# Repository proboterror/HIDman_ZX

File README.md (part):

# HIDman ZX
Адаптер USB и PS/2 клавиатур/мышей для ZX Spectrum.

## Входные требования:
- Разработать универсальный простой в повторении недорогой открытый интерфейс USB / PS/2 клавиатур и мышей.
- Должны поддерживаться как минимум два USB устройства одновременно
- Включает прошивку микроконтроллера, референсную минимальную схему включения и пример тестовой платы в KiCad
- Основной фокус на сопровождаемости прошивки микроконтроллера
- Выход интерфейса клавиатуры: сигналы матрицы переключателей A8-A15, D0-D4
- Выход интерфейсов Kempston Mouse и Kempston Joystick: сигналы DI0-DI7, стробы записи регистров MX, MY, MKEY, JOY

**Дополнительно:**
- Поддержка USB HID геймпадов как Kempston Joystick и для эмуляции кнопок клавиатуры
- Выход сигналов для управления кнопками эмулятора дисковода GOTEK по горячим кнопкам клавиатуры
- Выход сигналов управления Z80 по горячим кнопкам клавиатуры: BUSRQ (PAUSE), NMI(MAGIC), RESET

**Не входит в требования:**
- Реализация платы для ZX-BUS
- Реализация портов и регистров контроллеров ZX клавиатуры и Kempston Mouse
- Реализация защиты портов USB от статики / короткого замыкания / повышенного напряжения

## Реализация
В качестве основы проекта был взят проект [HIDman](https://github.com/rasteri/HIDman): USB HID to XT / AT / PS/2 / Serial converter : адаптер USB устройств в PS/2 keyboard/mouse device. От HIDman была взята реализация стека USB Host без модификаций.

Схема использует недорогие доступные чипы от [Nanjing Qinheng Microelectronics](https://www.wch-ic.com):
- 8-bit Enhanced USB MCU [CH559L](./doc/8-bit%20Enhanced%20USB%20MCU%20CH559%20Datasheet%201.6.pdf): расширенный Intel 8051 совместимый микроконтроллер с двумя аппаратными USB Host
- 8x16 Analog Switch Array Chip [CH446Q](./doc/8x16%20Analog%20Switch%20Array%20Chip%20CH446Q%20Datasheet%201D.pdf): матрица аналоговых ключей 8x16 с последовательным интерфейсом

В код добавлены:
- Реализация асинхронных интерфейсов PS/2 клавиатуры и мыши
- Реализация матрицы контактов 8x5 ZX Spectrum клавиатуры с раскладкой Xrust
- Интерфейс матрицы ключей CH446Q
- Интерфейс для контроллера Kempston Mouse (DI+MX/MY/MKEY)
- Интерфейс для контроллера Kempston Joystick (DI+JOY)
- Интерфейс управления Z80 (PAUSE/MAGIC/RESET) по клавишам F10/F11/F12
- Интерфейс управления кнопками GOTEK (RIGHT/LEFT/SELCT) по сочетанию клавиш CTRL+ RIGHT/LEFT/DOWN/UP

## Детали реализации

Тестовая плата для отладки присоединяется сверху к [ZX Spectrum Pentagon 128 2023/2024 Interface Board](https://github.com/proboterror/Pentagon_128_Interface_Board). Исходя из этого выбраны физические размеры и положение / распиновка разъема клавиатуры.

Интерфейс мыши расчитан на подсоединение к контроллеру, подобному [ZX_BUS_Mouse](https://github.com/proboterror/ZX_BUS_Mouse) с параллельной записью по шине 8-bit в регистры осей и колеса/кнопок. Колесо прокрутки мыши поддержано.

Исходный код поддержки PS/2 клавиатуры и интерфейса матрицы ZX Spectrum => CH446Q портирован из проекта расширенного интерфейса [ZX_RGBI2VGA-HDMI + GOTEK FlashFloppy I2C OSD + PS/2 Keyboard](https://github.com/proboterror/zx-rgbi-to-vga-hdmi_gotek-osd)

Исходный код поддержки PS/2 мыши портирован из экспериментальной ветки interrupt_processing_async проекта [ZX BUS Mouse](https://github.com/proboterror/ZX_BUS_Mouse/tree/interrupt_processing_async). Код обработки мыши по прерыванию clock в свою очередь основан на проекте Олега Трифонова [avr-mouse-ps2-to-serial](https://github.com/trol73/avr-mouse-ps2-to-serial). Код инициализации PS/2 мыши и основной цикл обработки событий асинхронный с минимальными задержками.

Тестирование показало, что MCU CH559L может работать от внутреннего генератора без использования внешнего кварцевого резонатора, выбор источника частоты из кода инициализации PLL.<br>
Конденсатор и резистор цепочки сброса MCU CH559L не нужны, т.к. есть внутренняя схема формирования сброса по питанию.

При тестировании проявился дефект: после подачи питания Gluk Reset Service всегда выводит экран Help, после нажатия Reset Z80 стартует нормально. Зажата клавиша 'A' ZX клавиатуры (адрес переключателя в матрице CH449Q 0x01) до момента программного зануления всех переключателей в CH449Q.<br>
В варианте с MCU RP2040 дефект не проявлялся.<br>
Расследование показало, что RP2040 при включении переводит (большинство) GPIO в режим input c pull-down (подтяжка к земле), выдавая логический '0' на GPIO pin. MCU CH559 при подаче питания активирует для портов pull-up резисторы (подтяжка к питанию 3.3V), выдавая логический '1' на выходы. Матрица переключателей CH446Q записывает значение сигнала DAT по адресу ранее выбранного переключателя при высоком уровне сигнала STB. Так как после аппаратного сброса CH446Q на входах STB и DAT был логический '1', то это приводило к нежелательной активации переключателя по адресу 0x01 (видимо в это значение сбрасывается внутренний регистр адреса).<br>
После подтяжки линии STB внешним резистором 10K к GND проблема почти решилась, но оставался нежелательный импульс длительностью 0.5 us в момент инициализации портов MCU. CH559 при сбросе инициализирует регистры P0..P3 выходного значения портов в значение 1111 1111b, и выстановка регистра P1 в 0x00 сразу после переключения порта P1 на выход приводила к такому эффекту. Исправлено выстановкой значения порта P1 до переключения его на выход.

## Режимы работы выходов
Входы / выходы матрицы клавиатуры A8-A15, D0-D4 и управляющих сигналов Z80 BUSRQ, NMI, RESET подключены к входам / выходам матрицы аналоговых ключей CH446Q. Общий вход X8 для сигналов Z80 BUSRQ, NMI, RESET подключен к GND.

Выходы кнопок GOTEK работают в режиме с открытым коллектором, при нажатии замыкают на GND.

Выход интерфейса Kempston Mouse и Kempston Joystick работает в режиме push-pull.

## Схема

## Тестовая плата

## Текущий статус
- В firmware реализована поддержка PS/2 и USB мышей и клавиатур.
- Поддерживаются беспроводные мыши / клавиатуры Logitech c Unified Receiver и им подобные, работающие как стандартный USB HID.
- Реализована поддержка геймпадов/джойстиков, совместимых с USB HID, в том числе Sony DualShock 4, Sony PlayStation 5 DualSense.
- Реализованы специальные драйверы для геймпадов Sony DualShock 3, XBox 360 USB Controller, XBox One / Series S/X Controller.
- Реализована экспериментальная поддержка SEGA Mega Drive / Genesis геймпада как 3-кнопочного.
- Проверена работа выходных портов мыши / клавиатуры / джойстика / GOTEK / Z80.
- Поддержка USB хабов и конфигурация беспроводная клавиатура/мышь + gamepad не тестировались, но заявлены в оригинальном проекте.
- События от геймпадов транслируются в нажатия кнопок клавиатуры и Kempston Joystick.
- Для контроллеров PS4 DualShock 4 и PS5 DualSense касания touchpad транслируются в движение мыши, второе касание в нажатие левой кнопки мыши, нажатие touchpad в нажатие правой кнопки мыши; левый аналоговый стик также транслируется в движение мыши, кнопки L1/R1 в нажатие кнопок мыши.
- Дополнительно реализовано масштабирование движения мыши 1:1, 1:2, 1:3 по клавишам F1, F2, F3. Не сохраняется при выключении.

## Известные проблемы

## ToDo
- Код обработки событий от PS/2 клавиатуры не обрабатывает ошибки parity. После тестирования стабильности работы уточнить необходимость отправки устройству PS/2 команды RESEND / RESET и очистки буфера ввода.
- Для контроллеров HID, XBox, PS3 добавить управление мышью левым аналоговым стиком, как для контроллеров PS4/5.
<hr>

# Вариант для шины ZX-BUS (Nemo-BUS)
Для большей осмысленности существования прошивки MCU и востребованности реализована плата в формате ZX-BUS с полной поддержкой всех возможностей прошивки.

Плата реализует интерфейсы клавиатуры, Kempston Mouse и Kempston Joystick (8 bit), позволяет подключить как минимум 2 USB устройства и PS/2 клавиатуру / мышь.<br>
Интерфейс клавиатуры работает одновременно с портом клавиатуры / магнитофона на основной плате компьютера.

## Схема

## Плата

## Выбор требований
- Плата должна содержать 2 порта USB и порты PS/2 мыши / клавиатуры, с возможностью подключения стандартных внешних планок.
- Использовать доступные и недорогие компоненты.
- Высота платы должна быть минимально возможной, максимальна ширина / высота 99 мм.
- Предусмотреть защиту портов от короткого замыкания (PS/2 / USB) и статического электричества (USB). Плата должна быть работоспособна без запаянных элементов защиты портов USB от статического электричества.
- Порт Kempston Joystick должен быть отключаемый по причине потенциальных конфликтов / не нужности.
- Штыревые разъемы не обязательны к запайке.
- SMD конденсаторы и резисторы форм фактора 1206 для удобства ручной сборки.

## Детали реализации
Матрица переключателей клавиатуры и специальных кнопок вместо отдельного чипа CH446Q помещена в CPLD вместе с дешифраторам адресов и регистрами интерфейсов, с сохранением последовательного интерфейса для доступа (drop-in replacement).

CPLD Altera EPM3128ATC100 выбрана исходя из доступности и минимальной необходимой емкости в макроячейках.<br>

Текущая реализация использует неполную дешифрацию портов клавиатуры, Kempston Mouse, Kempston Joystick.<br>
В идеале для Kempston Joystick желательна полная дешифрация нижних 8 бит адреса порта #1F, но для этого нужна нетривиальная оптимизация.<br>

Плата не блокирует встроенные порты клавиатуры и магнитофона для их параллельной работы.<br>
Плата полностью блокирует встроенный порт Kempston Joystick и порты Kempston Mouse; можно отредактировать описание для параллельной работы интерфейсов Kempston Joystick.<br>
Интерфейс клавиатуры для разделения шины данных подключается к шине в режиме с открытым коллектором.

Использовано порядка 107 из 128 макроячеек. Сложность описания и потребление элементарных компонентов (AND, OR, MUX, tri-state) в выходной RTL map требует особого внимания, при увеличении сложности fitter не может распределить ресурсы CPLD.<br>
Описание схемы в CPLD и testbench для тестирования написаны на языке System Verilog.

Интерфейс Kempston Joystick восьмибитный (4 направления + 4 кнопки) и по умолчанию отключен, включение через jumper / solder jumper.

Интерфейс мыши полный с поддержкой колеса мыши и трех кнопок.

Сигнал IORQGE/ буферизирован до уровня 5V через tri-state буфер 74LVC1G125DB.<br>
Сигналы PAUSE, MAGIC, RESET от CPLD буферизированы на сигналы шины Z80 BUSRQ/, NMI/, RST через FET транзисторные ключи BSS123.

Набор и форма разъемов выбраны исходя из минимальной высоты платы и потенциальной востребованности.<br>
По этой причине разъем PS/2 mini DIN 6 pin комбинированный: PS/2 мышь может быть подключена напрямую, для подключения PS/2 клавиатуры потребуется доступный недорогой Y splitter cable.

Разъемы USB компактные вертикальные [Würth Elektronik 614004134726](https://www.we-online.com/en/components/products/COM_TYPE_A_UP_RIGHT#614004134726) или их распространенные [аналоги](https://aliexpress.ru/item/1005003752018041.html?sku_id=12000028387034115).

Сигналы обоих портов USB и PS/2 мыши / клавиатуры также выведены на штыревые разъемы для подключения стандартных внешних планок/выбросов для двух портов USB или отдельных портов PS/2.

Контроллер Kempston Joystick при его разрешении может конфликтовать с контроллером TR-DOS.
На примере Pentagon-128 2024 встроенный порт Kempston для разрешения конфликта использует сигнал OIRQ/, который по сути своей (почти) противоположен сигналу DOS/.

Соответственно как вариант решения сигнал DOS/ был включен в дешифрацию порта:
```
	// Port #1F/31 xxxxxxxx00011111 
	wire address_match = (A[7] | A[6] | A[5] | ~M1 | ~DOS | JOY_ENABLE);
```

## Схема сброса CPLD
Важный момент, в многих реализациях игнорируемый.<br>
Для корректной работы ПО в ROM, исполняемого сразу после _включения_ компьютера, например Gluk Reset Service, требуется чтобы регистры матрицы клавиатуры и контроллера Kempston Mouse содержали корректные значения почти сразу после включения (порядка 24 ms): микроконтроллер интерфейса не успевает обновить их значения.<br>
Необходим внутрисхемный сброс регистров CPLD в нужное состояние по системному сигналу RESET _или_ самостоятельное формирование сигнала сброса при включении.<br>
Выбран второй вариант, т.к. CPLD также может формировать системный сигнал RESET (RST_OUT) исходя из значения внутреннего регистра, и это может вводить циклическую зависимость.

Сброс происходит по нисходящему фронту сигнала (более правильно было бы по уровню сигнала).

## Защита портов
Защита портов USB / PS/2 от короткого замыкания: самовосстанавливающийся предохранитель форм-фактора 1812 (Littelfuse 1812L050PR, 0.5A, 15V) (номинал требует уточнения, предельная нагрузка отдельного порта USB 0.5A@5V, возможно заменить на Bourns MF-NSMF075-2, 0.75 А, 6V, 1206).

Защита портов USB от статического электричества: [IP4220CZ6 Dual USB 2.0 ESD Protection TVS Array](doc/IP4220CZ6%20Dual%20USB%202.0%20integrated%20ESD%20protection%20[NXP].pdf). Может быть не установлена.<br>
В плате версии 1.0 подключена некорректно (?) и не должна устанавливаться.<br>
В плате версии 1.1 подключена в соответствии с datasheet, но блокирует порт USB для прошивки MCU.

## Зарезервированные сигналы
В CPLD заведены, но не используются сигналы шины ZX-BUS: CLK.<br>
Также заведен сигнал DOS/. Сигнал присутствует только на шине Nemo-BUS xUSSR клонов, в оригинальных моделях ZX-Spectrum с шиной ZX-BUS на этом контакте напряжение питания +9V. Чтобы обратить внимание на этот момент, сигнал подключен через замкнутый solder jumper.

## Порт Tape In
Порт входа магнитофона подключен к 6 биту порта #FE клавиатуры, соответственно при блокировке внутреннего порта клавитуры потенциально отключается и порт магнитофона.<br>
Для экспериментов на плате выведен разъем TAPE_IN. К порту можно подключить только LVTTL 3.3V сигнал, например от эмулятора магнитофона на TZXDuino.

## Текущий статус
- Прошивка CPLD проверена через testbench в ModelSim: опция "Tools/Run EDA Simulation Tool/EDA RTL Simulation" в Quartus. Должен быть установлен ModelSim из дистрибутива Quartus (использовалась версия 13.0sp1).
- Платы собраны и протестированы.
- Протестированы контроллеры Kempston Mouse, Kempston Joystick, ZX матричной клавиатуры: работают, корректно сбрасываются при включении. Реализация матрицы клавиатуры позволяет зажимать много кнопок без эффекта фантомных нажатий, в том числе при маппинге с HID геймпада.
- Клавиатура работает параллельно с портом клавиатуры и магнитофона на основной плате.
- Работа сигналов PAUSE, MAGIC, RESET через транзисторные ключи на шину проверена.
- Работа TTL входа TAPE_IN не проверена.
- ESD защита портов блокирует работу USB и не должна устанавливаться.

## Известные проблемы
См. описание в истории коммитов до реализации порта клавиатуры с открытым коллектором.

## Сборка проекта
Для сборки прошивки из исходников потребуются: компилятор SDCC 3.9.3, GNU утилиты в составе msys2.
- Скопировать / установить [SDCC 3.9.3](https://github.com/atc1441/CH559sdccUSBHost/tree/master/SDCC). Добавить путь к SDCC/bin в переменную окружения PATH.
- Установить [MSYS2](https://www.msys2.org/). Путь к msys64/usr/bin должен быть в PATH.

Компиляция:
```
cd firmware
build-release.bat
```
Файлы прошивки сохраняются в каталоге firmware/out

## Прошивка CH559L
Необходимо установить [WCH ISP Studio](https://www.wch.cn/downloads/WCHISPTool_Setup_exe.html)
См. оригинальную инструкцию по прошивке ниже.

Потребуется кабель USB A - USB A (вилка - вилка).

Вход в режим програмирования:
- Запустить WCH ISP Studio, выбрать режим 
- Отсоединить контроллер от внешнего питания / устройств
- Замкнуть jumper BOOT0 (P4.6)
- Подключить контроллер через разъем USB_B к ПК
- Контроллер должен появиться в списке Dev list
- При неудаче повторить

Программирование:
- Выбрать файл прошивки
- Нажать Download
- При неудаче повторить

Примечания:
- Процедура прошивки может быть нестабильной / очень нестабильной в зависимости от контроллера USB в ПК.
- Вход в режим программирования через запуск bootloader'а прошивкой при сбросе (BOOT1 + RESET) не тестировался.
- Для CH559L заявлена поддержка serial programmer, есть опция в WCH ISP Studio и доступен инструмент [CH55x_python_flasher](https://github.com/hexeguitar/CH55x_python_flasher) для Windows / Linux (работа chflasher подтверждена).

## Схожие проекты
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
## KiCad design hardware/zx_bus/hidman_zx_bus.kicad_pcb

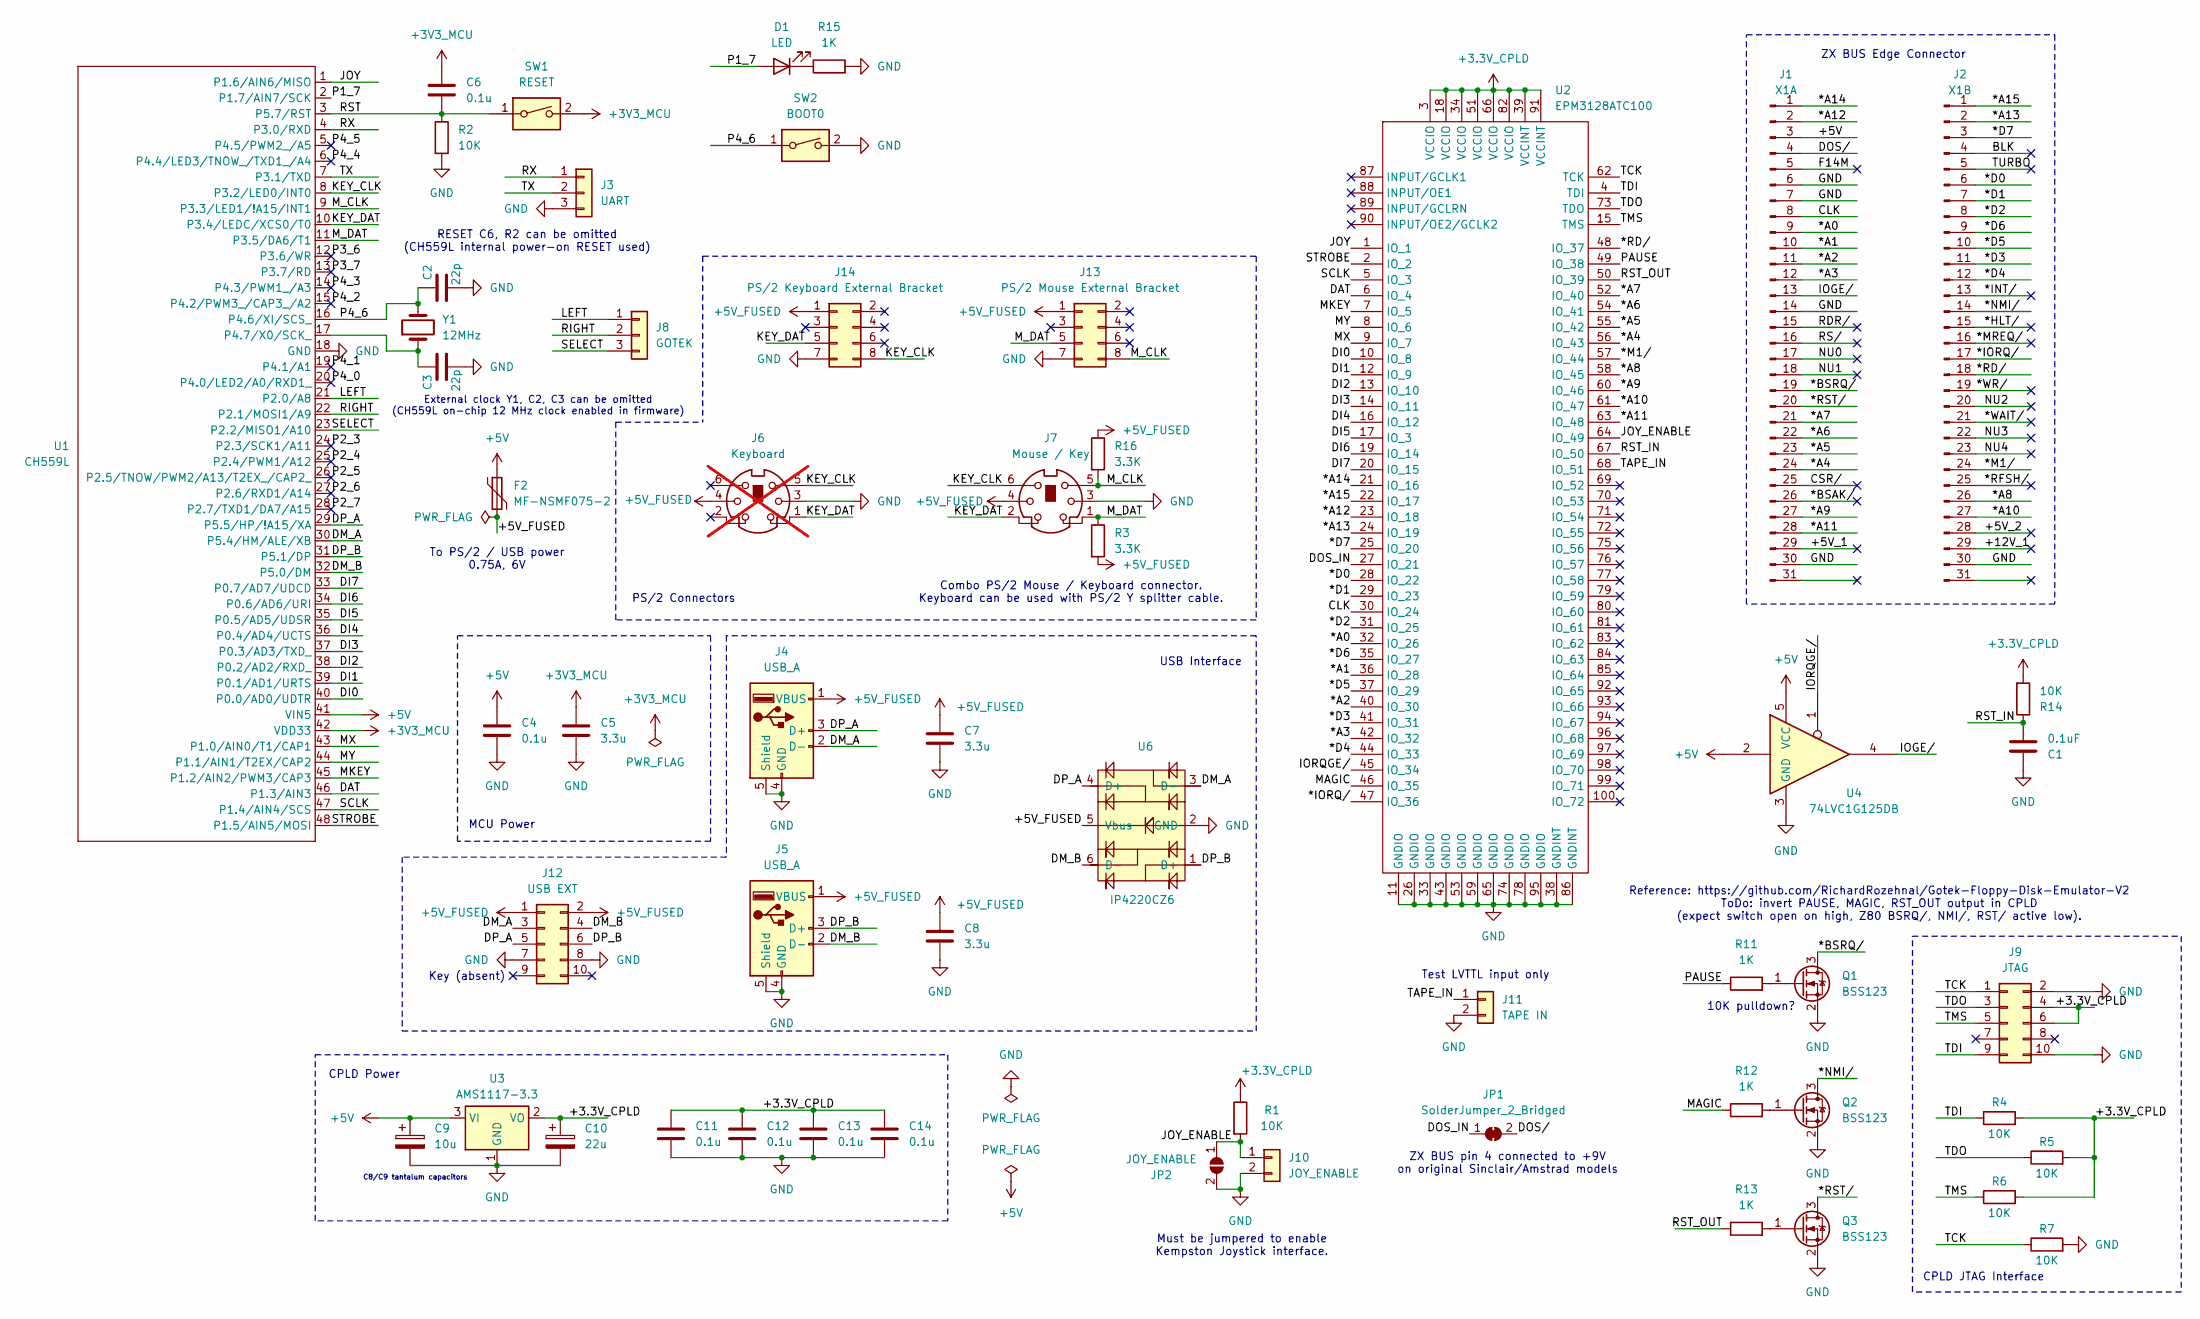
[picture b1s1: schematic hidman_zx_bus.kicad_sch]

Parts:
C1: 0.1uF; C_1206_3216Metric_Pad1.33x1.80mm_HandSolder
C2, C3: 22p; C_1206_3216Metric_Pad1.33x1.80mm_HandSolder
C4, C6, C11, C12, C13, C14: 0.1u; C_1206_3216Metric_Pad1.33x1.80mm_HandSolder
C5, C7, C8: 3.3u; C_1206_3216Metric_Pad1.33x1.80mm_HandSolder
C9: 10u; CP_EIA-6032-28_Kemet-C_Pad2.25x2.35mm_HandSolder
C10: 22u; CP_EIA-6032-28_Kemet-C_Pad2.25x2.35mm_HandSolder
D1: LED; LED_1206_3216Metric_Pad1.42x1.75mm_HandSolder
F2: MF-NSMF075-2; Fuse_1206_3216Metric_Pad1.42x1.75mm_HandSolder
J1: X1A; PinSocket_1x31_P2.54mm_2
J2: X1B; PinSocket_1x31_P2.54mm_2
J3: UART; PinHeader_1x03_P2.54mm_Vertical
J4, J5: USB_A; USB_A_Wuerth_614004134726_Horizontal
J6: Keyboard; Connector_Mini-DIN_Female_6Pin_2rows; not fitted
J7: Mouse / Key; Connector_Mini-DIN_Female_6Pin_2rows
J8: GOTEK; PinHeader_1x03_P2.54mm_Vertical
J9: JTAG; IDC-Header_2x05_P2.54mm_Vertical
J10: JOY_ENABLE; PinHeader_1x02_P2.54mm_Vertical
J11: TAPE IN; PinHeader_1x02_P2.54mm_Vertical
J12: USB EXT; PinHeader_2x05_P2.54mm_Vertical
J13: PS/2 Mouse External Bracket; PinHeader_2x04_P2.54mm_Vertical
J14: PS/2 Keyboard External Bracket; PinHeader_2x04_P2.54mm_Vertical
JP1: SolderJumper_2_Bridged; SolderJumper-2_P1.3mm_Bridged_RoundedPad1.0x1.5mm
JP2: JOY_ENABLE; SolderJumper-2_P1.3mm_Open_RoundedPad1.0x1.5mm
Q1, Q2, Q3: BSS123; SOT-23
R1, R2, R4, R5, R6, R7, R14: 10K; R_1206_3216Metric_Pad1.30x1.75mm_HandSolder
R3, R16: 3.3K; R_1206_3216Metric_Pad1.30x1.75mm_HandSolder
R11, R12, R13, R15: 1K; R_1206_3216Metric_Pad1.30x1.75mm_HandSolder
SW1: RESET; PinHeader_1x02_P2.54mm_Vertical
SW2: BOOT0; PinHeader_1x02_P2.54mm_Vertical
U1: CH559L; LQFP-48_7x7mm_P0.5mm
U2: EPM3128ATC100; TQFP-100_14x14mm_P0.5mm
U3: AMS1117-3.3; SOT-223-3_TabPin2
U4: 74LVC1G125DB; SOT-23-5_HandSoldering
U6: IP4220CZ6; TSOP-6_1.65x3.05mm_P0.95mm
Y1: 12MHz; Crystal_HC49-4H_Vertical

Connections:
+3.3V_CPLD: C10.1, C11.1, C12.1, C13.1, C14.1, J9.4, J9.6, R1.1, R4.2, R5.2, R6.2, R14.2, U2.3 (VCCIO), U2.18 (VCCIO), U2.34 (VCCIO), U2.39 (VCCINT), U2.51 (VCCIO), U2.66 (VCCIO), U2.82 (VCCIO), U2.91 (VCCINT), U3.2 (VO)
+3V3_MCU: C5.1, C6.1, SW1.2, U1.42 (VDD33)
+5V: C4.1, C9.1, F2.1, J1.3, U1.41 (VIN5), U3.3 (VI), U4.2, U4.5 (VCC)
+5V_FUSED: C7.1, C8.1, F2.2, J4.1 (VBUS), J5.1 (VBUS), J6.4, J7.4, J12.1, J12.2, J13.1, J14.1, R3.2, R16.1, U6.5 (Vbus)
/*A0: J1.9, U2.32 (IO_26)
/*A1: J1.10, U2.36 (IO_28)
/*A2: J1.11, U2.40 (IO_30)
/*A3: J1.12, U2.42 (IO_32)
/*A4: J1.24, U2.56 (IO_43)
/*A5: J1.23, U2.55 (IO_42)
/*A6: J1.22, U2.54 (IO_41)
/*A7: J1.21, U2.52 (IO_40)
/*A8: J2.26, U2.58 (IO_45)
/*A9: J1.27, U2.60 (IO_46)
/*A10: J2.27, U2.61 (IO_47)
/*A11: J1.28, U2.63 (IO_48)
/*A12: J1.2, U2.23 (IO_18)
/*A13: J2.2, U2.24 (IO_19)
/*A14: J1.1, U2.21 (IO_16)
/*A15: J2.1, U2.22 (IO_17)
/*BSAK/: J1.26
/*BSRQ/: J1.19, Q1.3 (D)
/*D0: J2.6, U2.28 (IO_22)
/*D1: J2.7, U2.29 (IO_23)
/*D2: J2.8, U2.31 (IO_25)
/*D3: J2.11, U2.41 (IO_31)
/*D4: J2.12, U2.44 (IO_33)
/*D5: J2.10, U2.37 (IO_29)
/*D6: J2.9, U2.35 (IO_27)
/*D7: J2.3, U2.25 (IO_20)
/*HLT/: J2.15
/*INT/: J2.13
/*IORQ/: J2.17, U2.47 (IO_36)
/*M1/: J2.24, U2.57 (IO_44)
/*MREQ/: J2.16
/*NMI/: J2.14, Q2.3 (D)
/*RD/: J2.18, U2.48 (IO_37)
/*RFSH/: J2.25
/*RST/: J1.20, Q3.3 (D)
/*WAIT/: J2.21
/*WR/: J2.19
/+5V_1: J1.29
/+5V_2: J2.28
/+12V_1: J2.29
/BLK: J2.4
/CLK: J1.8, U2.30 (IO_24)
/CSR/: J1.25
/DAT: U1.46 (P1.3/AIN3), U2.6 (IO_4)
/DI0: U1.40 (P0.0/AD0/UDTR), U2.10 (IO_8)
/DI1: U1.39 (P0.1/AD1/URTS), U2.12 (IO_9)
/DI2: U1.38 (P0.2/AD2/RXD_), U2.13 (IO_10)
/DI3: U1.37 (P0.3/AD3/TXD_), U2.14 (IO_11)
/DI4: U1.36 (P0.4/AD4/UCTS), U2.16 (IO_12)
/DI5: U1.35 (P0.5/AD5/UDSR), U2.17 (IO_3)
/DI6: U1.34 (P0.6/AD6/URI), U2.19 (IO_14)
/DI7: U1.33 (P0.7/AD7/UDCD), U2.20 (IO_15)
/DM_A: J4.2 (D-), J12.3, U1.30 (P5.4/HM/ALE/XB), U6.3 (D-)
/DM_B: J5.2 (D-), J12.4, U1.32 (P5.0/DM), U6.6 (D-)
/DOS_IN: JP1.1 (A), U2.27 (IO_21)
/DOS/: J1.4, JP1.2 (B)
/DP_A: J4.3 (D+), J12.5, U1.29 (P5.5/HP/!A15/XA), U6.4 (D+)
/DP_B: J5.3 (D+), J12.6, U1.31 (P5.1/DP), U6.1 (D+)
/F14M: J1.5
/IOGE/: J1.13, U4.4
/IORQGE/: U2.45 (IO_34), U4.1
/JOY: U1.1 (P1.6/AIN6/MISO), U2.1 (IO_1)
/JOY_ENABLE: J10.1, JP2.1 (A), R1.2, U2.64 (IO_49)
/KEY_CLK: J6.5, J7.6, J14.8, U1.8 (P3.2/LED0/INT0)
/KEY_DAT: J6.1, J7.2, J14.5, U1.10 (P3.4/LEDC/XCS0/T0)
/LEFT: J8.1, U1.21 (P2.0/A8)
/MAGIC: R12.1, U2.46 (IO_35)
/MKEY: U1.45 (P1.2/AIN2/PWM3/CAP3), U2.7 (IO_5)
/MX: U1.43 (P1.0/AIN0/T1/CAP1), U2.9 (IO_7)
/MY: U1.44 (P1.1/AIN1/T2EX/CAP2), U2.8 (IO_6)
/M_CLK: J7.5, J13.8, R16.2, U1.9 (P3.3/LED1/!A15/INT1)
/M_DAT: J7.1, J13.5, R3.1, U1.11 (P3.5/DA6/T1)
/NU0: J1.17
/NU1: J1.18
/NU2: J2.20
/NU3: J2.22
/NU4: J2.23
/P1_7: D1.2 (A), U1.2 (P1.7/AIN7/SCK)
/P2_3: U1.24 (P2.3/SCK1/A11)
/P2_4: U1.25 (P2.4/PWM1/A12)
/P2_5: U1.26 (P2.5/TNOW/PWM2/A13/T2EX_/CAP2_)
/P2_6: U1.27 (P2.6/RXD1/A14)
/P2_7: U1.28 (P2.7/TXD1/DA7/A15)
/P3_6: U1.12 (P3.6/WR)
/P3_7: U1.13 (P3.7/RD)
/P4_0: U1.20 (P4.0/LED2/A0/RXD1_)
/P4_1: U1.19 (P4.1/A1)
/P4_2: U1.15 (P4.2/PWM3_/CAP3_/A2)
/P4_3: U1.14 (P4.3/PWM1_/A3)
/P4_4: U1.6 (P4.4/LED3/TNOW_/TXD1_/A4)
/P4_5: U1.5 (P4.5/PWM2_/A5)
/P4_6: C2.1, SW2.1, U1.16 (P4.6/XI/SCS_), Y1.2
/PAUSE: R11.1, U2.49 (IO_38)
/RDR/: J1.15
/RIGHT: J8.2, U1.22 (P2.1/MOSI1/A9)
/RST: C6.2, R2.1, SW1.1, U1.3 (P5.7/RST)
/RST_IN: C1.2, R14.1, U2.67 (IO_50)
/RST_OUT: R13.1, U2.50 (IO_39)
/RS/: J1.16
/RX: J3.1, U1.4 (P3.0/RXD)
/SCLK: U1.47 (P1.4/AIN4/SCS), U2.5 (IO_3)
/SELECT: J8.3, U1.23 (P2.2/MISO1/A10)
/STROBE: U1.48 (P1.5/AIN5/MOSI), U2.2 (IO_2)
/TAPE_IN: J11.1, U2.68 (IO_51)
/TCK: J9.1, R7.1, U2.62 (TCK)
/TDI: J9.9, R4.1, U2.4 (TDI)
/TDO: J9.3, R5.1, U2.73 (TDO)
/TMS: J9.5, R6.1, U2.15 (TMS)
/TURBO: J2.5
/TX: J3.2, U1.7 (P3.1/TXD)
GND: C1.1, C2.2, C3.2, C4.2, C5.2, C7.2, C8.2, C9.2, C10.2, C11.2, C12.2, C13.2, C14.2, J1.6, J1.7, J1.14, J1.30, J2.30, J3.3, J4.4 (GND), J4.5 (Shield), J5.4 (GND), J5.5 (Shield), J6.3, J7.3, J9.2, J9.10, J10.2, J11.2, J12.7, J12.8, J13.7, J14.7, JP2.2 (B), Q1.2 (S), Q2.2 (S), Q3.2 (S), R2.2, R7.2, R15.2, SW2.2, U1.18 (GND), U2.11 (GNDIO), U2.26 (GNDIO), U2.33 (GNDIO), U2.38 (GNDINT), U2.43 (GNDIO), U2.53 (GNDIO), U2.59 (GNDIO), U2.65 (GNDIO), U2.74 (GNDIO), U2.78 (GNDIO), U2.86 (GNDINT), U2.95 (GNDIO), U3.1 (GND), U4.3 (GND), U6.2 (GND)
unnamed: D1.1 (K), R15.1
unnamed: Q1.1 (G), R11.2
unnamed: Q2.1 (G), R12.2
unnamed: Q3.1 (G), R13.2
unnamed: C3.1, U1.17 (P4.7/X0/SCK_), Y1.1

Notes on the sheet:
ZX BUS Edge Connector
CPLD Power
Must be jumpered to enable Kempston Joystick interface.
External clock Y1, C2, C3 can be omitted (CH559L on-chip 12 MHz clock enabled in firmware)
USB Interface
Key (absent)
Reference: https://github.com/RichardRozehnal/Gotek-Floppy-Disk-Emulator-V2 ToDo: invert PAUSE, MAGIC, RST_OUT output in CPLD (expect switch open on high, Z80 BSRQ/, NMI/, RST/ active low).
MCU Power
RESET C6, R2 can be omitted (CH559L internal power-on RESET used)
CPLD JTAG Interface
ZX BUS pin 4 connected to +9V on original Sinclair/Amstrad models
Combo PS/2 Mouse / Keyboard connector. Keyboard can be used with PS/2 Y splitter cable.
Test LVTTL input only
PS/2 Connectors
To PS/2 / USB power 0.75A, 6V
10K pulldown?
C8/C9 tantalum capacitors

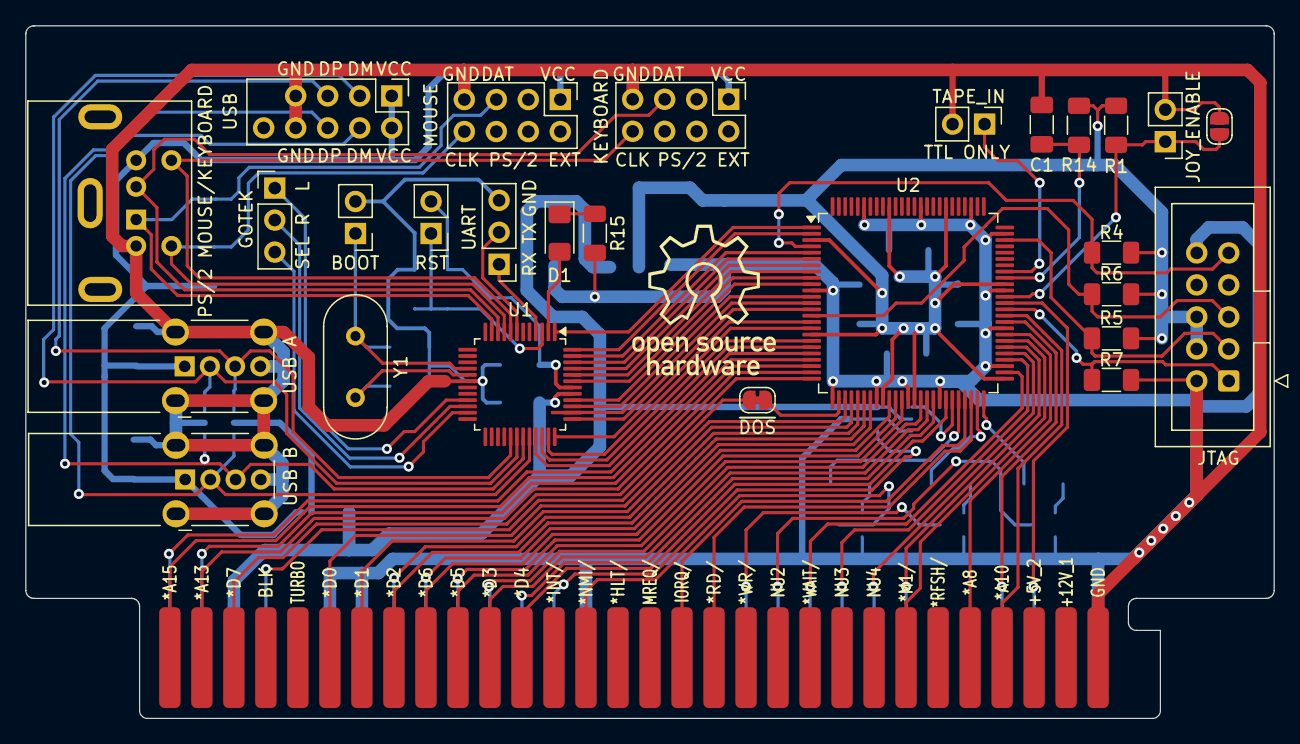
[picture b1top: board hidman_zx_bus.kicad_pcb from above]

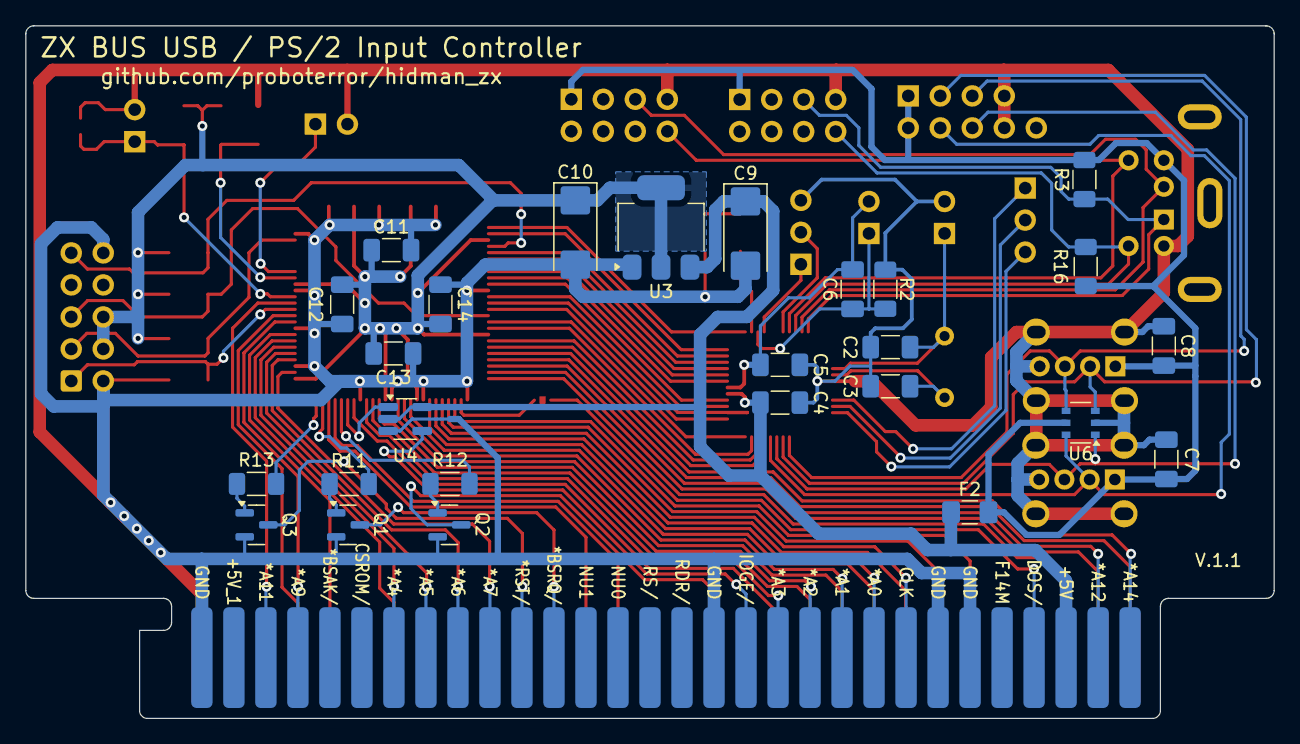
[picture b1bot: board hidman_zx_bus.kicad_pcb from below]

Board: 2 copper layers, 99.1 x 55.0 mm, 55 parts (27 on the bottom side), 86 nets.

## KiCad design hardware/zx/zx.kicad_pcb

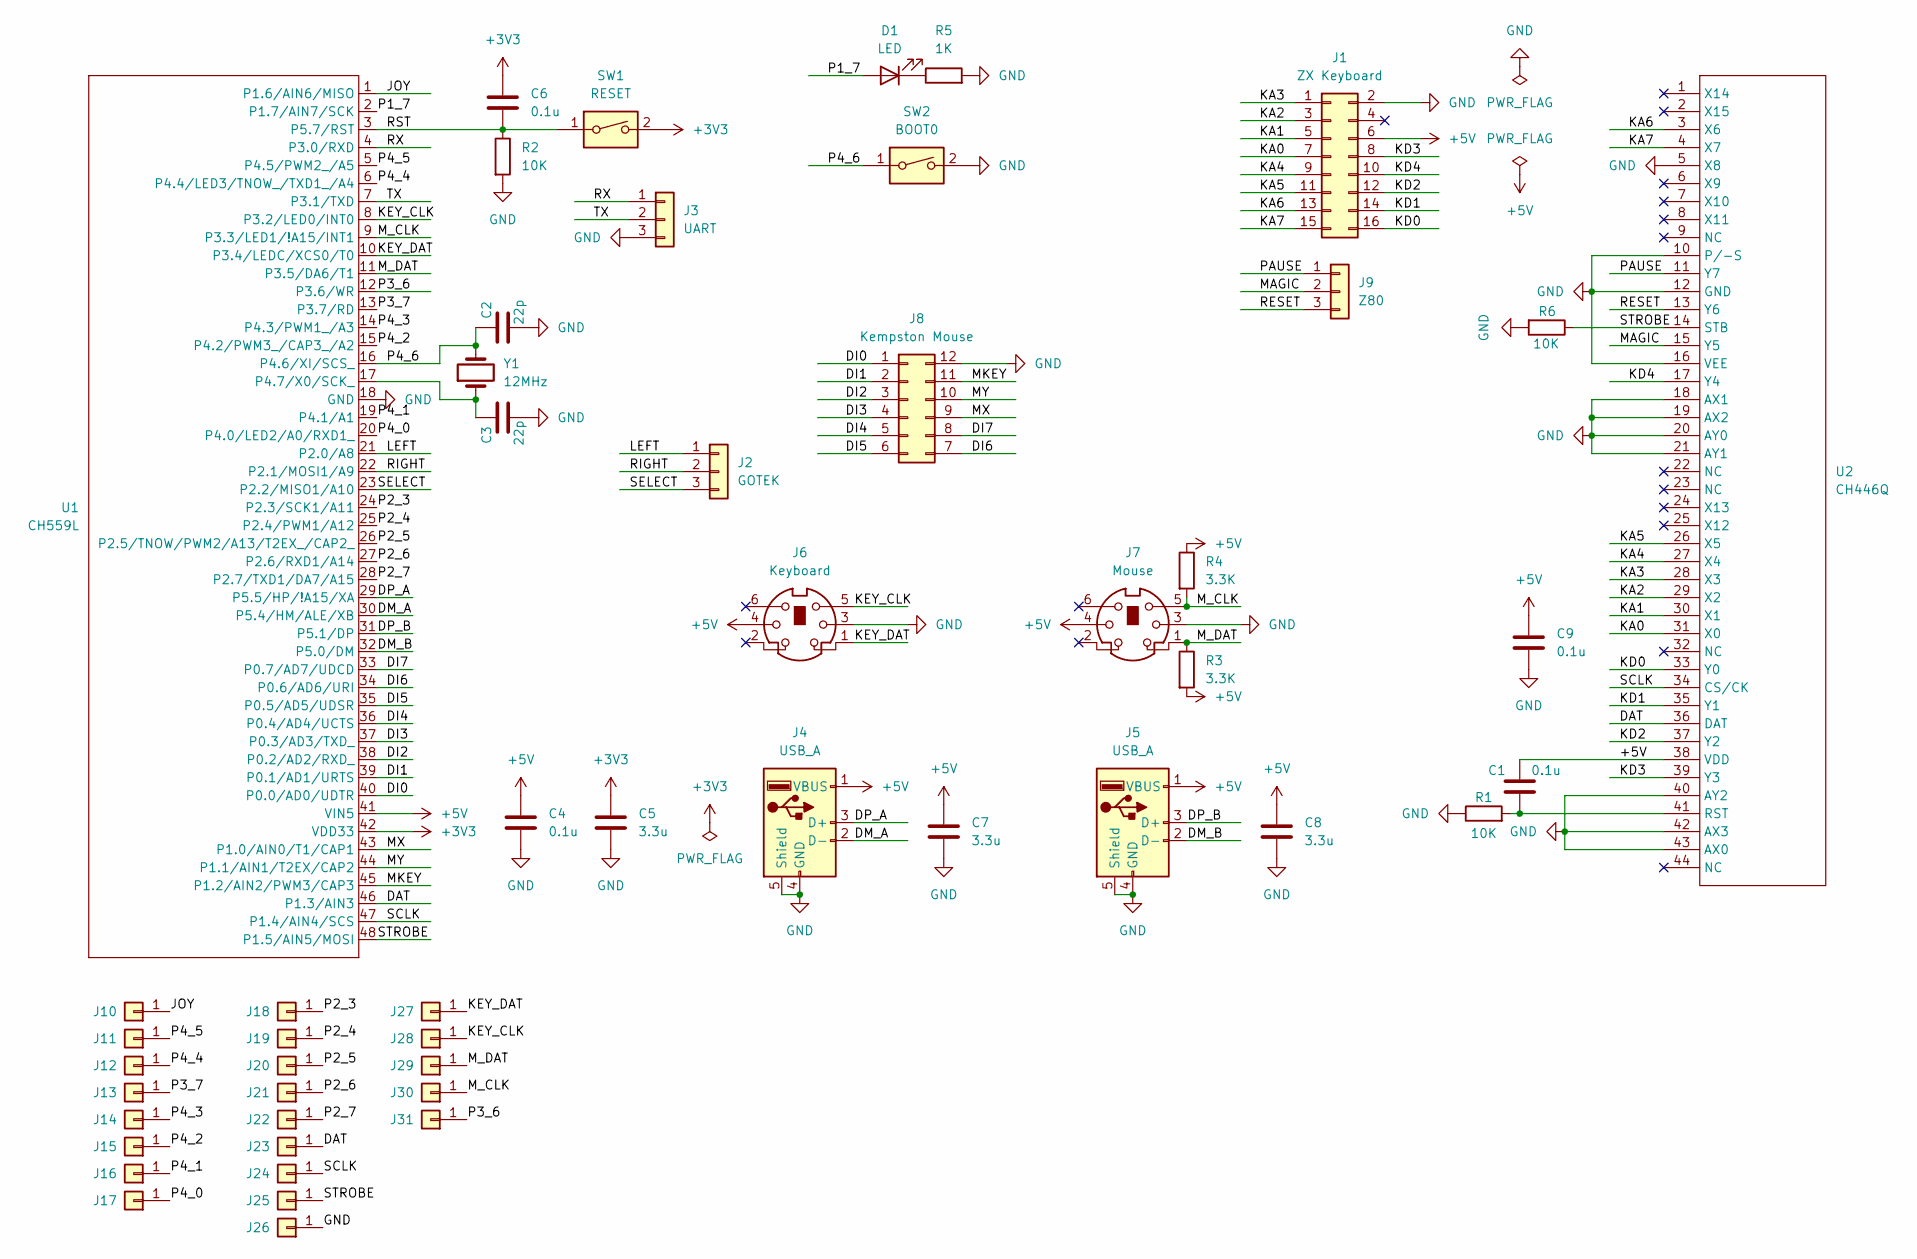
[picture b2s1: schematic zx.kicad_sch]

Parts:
C1, C4, C6, C9: 0.1u; C_1206_3216Metric_Pad1.33x1.80mm_HandSolder
C2, C3: 22p; C_1206_3216Metric_Pad1.33x1.80mm_HandSolder
C5, C7, C8: 3.3u; C_1206_3216Metric_Pad1.33x1.80mm_HandSolder
D1: LED; LED_1206_3216Metric_Pad1.42x1.75mm_HandSolder
J1: ZX Keyboard; PinHeader_2x08_P2.54mm_Vertical
J2: GOTEK; PinHeader_1x03_P2.54mm_Vertical
J3: UART; PinHeader_1x03_P2.54mm_Vertical
J4, J5: USB_A; USB_A_Stewart_SS-52100-001_Horizontal
J6: Keyboard; Connector_Mini-DIN_Female_6Pin_2rows
J7: Mouse; Connector_Mini-DIN_Female_6Pin_2rows
J8: Kempston Mouse; PinHeader_2x06_P2.54mm_Vertical
J9: Z80; PinHeader_1x03_P2.54mm_Vertical
J10, J11, J12, J13, J14, J15, J16, J17, J18, J19, J20, J21, J22, J23, J24, J25, J26, J27, J28, J29, J30, J31: Conn_01x01; THT_Pin_Vertical
R1, R2, R6: 10K; R_1206_3216Metric_Pad1.30x1.75mm_HandSolder
R3, R4: 3.3K; R_1206_3216Metric_Pad1.30x1.75mm_HandSolder
R5: 1K; R_1206_3216Metric_Pad1.30x1.75mm_HandSolder
SW1: RESET; PinHeader_1x02_P2.54mm_Vertical
SW2: BOOT0; PinHeader_1x02_P2.54mm_Vertical
U1: CH559L; LQFP-48_7x7mm_P0.5mm
U2: CH446Q; TQFP-44_10x10mm_P0.8mm
Y1: 12MHz; Crystal_HC49-4H_Vertical

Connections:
+3V3: C5.1, C6.1, SW1.2, U1.42 (VDD33)
+5V: C1.1, C4.1, C7.1, C8.1, C9.1, J1.6, J4.1 (VBUS), J5.1 (VBUS), J6.4, J7.4, R3.2, R4.1, U1.41 (VIN5), U2.38 (VDD)
/DAT: J23.1, U1.46 (P1.3/AIN3), U2.36 (DAT)
/DI0: J8.1, U1.40 (P0.0/AD0/UDTR)
/DI1: J8.2, U1.39 (P0.1/AD1/URTS)
/DI2: J8.3, U1.38 (P0.2/AD2/RXD_)
/DI3: J8.4, U1.37 (P0.3/AD3/TXD_)
/DI4: J8.5, U1.36 (P0.4/AD4/UCTS)
/DI5: J8.6, U1.35 (P0.5/AD5/UDSR)
/DI6: J8.7, U1.34 (P0.6/AD6/URI)
/DI7: J8.8, U1.33 (P0.7/AD7/UDCD)
/DM_A: J4.2 (D-), U1.30 (P5.4/HM/ALE/XB)
/DM_B: J5.2 (D-), U1.32 (P5.0/DM)
/DP_A: J4.3 (D+), U1.29 (P5.5/HP/!A15/XA)
/DP_B: J5.3 (D+), U1.31 (P5.1/DP)
/JOY: J10.1, U1.1 (P1.6/AIN6/MISO)
/KA0: J1.7, U2.31 (X0)
/KA1: J1.5, U2.30 (X1)
/KA2: J1.3, U2.29 (X2)
/KA3: J1.1, U2.28 (X3)
/KA4: J1.9, U2.27 (X4)
/KA5: J1.11, U2.26 (X5)
/KA6: J1.13, U2.3 (X6)
/KA7: J1.15, U2.4 (X7)
/KD0: J1.16, U2.33 (Y0)
/KD1: J1.14, U2.35 (Y1)
/KD2: J1.12, U2.37 (Y2)
/KD3: J1.8, U2.39 (Y3)
/KD4: J1.10, U2.17 (Y4)
/KEY_CLK: J6.5, J28.1, U1.8 (P3.2/LED0/INT0)
/KEY_DAT: J6.1, J27.1, U1.10 (P3.4/LEDC/XCS0/T0)
/LEFT: J2.1, U1.21 (P2.0/A8)
/MAGIC: J9.2, U2.15 (Y5)
/MKEY: J8.11, U1.45 (P1.2/AIN2/PWM3/CAP3)
/MX: J8.9, U1.43 (P1.0/AIN0/T1/CAP1)
/MY: J8.10, U1.44 (P1.1/AIN1/T2EX/CAP2)
/M_CLK: J7.5, J30.1, R4.2, U1.9 (P3.3/LED1/!A15/INT1)
/M_DAT: J7.1, J29.1, R3.1, U1.11 (P3.5/DA6/T1)
/P1_7: D1.2 (A), U1.2 (P1.7/AIN7/SCK)
/P2_3: J18.1, U1.24 (P2.3/SCK1/A11)
/P2_4: J19.1, U1.25 (P2.4/PWM1/A12)
/P2_5: J20.1, U1.26 (P2.5/TNOW/PWM2/A13/T2EX_/CAP2_)
/P2_6: J21.1, U1.27 (P2.6/RXD1/A14)
/P2_7: J22.1, U1.28 (P2.7/TXD1/DA7/A15)
/P3_6: J31.1, U1.12 (P3.6/WR)
/P3_7: J13.1, U1.13 (P3.7/RD)
/P4_0: J17.1, U1.20 (P4.0/LED2/A0/RXD1_)
/P4_1: J16.1, U1.19 (P4.1/A1)
/P4_2: J15.1, U1.15 (P4.2/PWM3_/CAP3_/A2)
/P4_3: J14.1, U1.14 (P4.3/PWM1_/A3)
/P4_4: J12.1, U1.6 (P4.4/LED3/TNOW_/TXD1_/A4)
/P4_5: J11.1, U1.5 (P4.5/PWM2_/A5)
/P4_6: C2.1, SW2.1, U1.16 (P4.6/XI/SCS_), Y1.2
/PAUSE: J9.1, U2.11 (Y7)
/RESET: J9.3, U2.13 (Y6)
/RIGHT: J2.2, U1.22 (P2.1/MOSI1/A9)
/RST: C6.2, R2.1, SW1.1, U1.3 (P5.7/RST)
/RX: J3.1, U1.4 (P3.0/RXD)
/SCLK: J24.1, U1.47 (P1.4/AIN4/SCS), U2.34 (CS/CK)
/SELECT: J2.3, U1.23 (P2.2/MISO1/A10)
/STROBE: J25.1, R6.1, U1.48 (P1.5/AIN5/MOSI), U2.14 (STB)
/TX: J3.2, U1.7 (P3.1/TXD)
GND: C2.2, C3.2, C4.2, C5.2, C7.2, C8.2, C9.2, J1.2, J3.3, J4.4 (GND), J4.5 (Shield), J5.4 (GND), J5.5 (Shield), J6.3, J7.3, J8.12, J26.1, R1.1, R2.2, R5.2, R6.2, SW2.2, U1.18 (GND), U2.5 (X8), U2.10 (P/-S), U2.12 (GND), U2.16 (VEE), U2.18 (AX1), U2.19 (AX2), U2.20 (AY0), U2.21 (AY1), U2.40 (AY2), U2.42 (AX3), U2.43 (AX0)
unnamed: D1.1 (K), R5.1
unnamed: C3.1, U1.17 (P4.7/X0/SCK_), Y1.1
unnamed: C1.2, R1.2, U2.41 (RST)

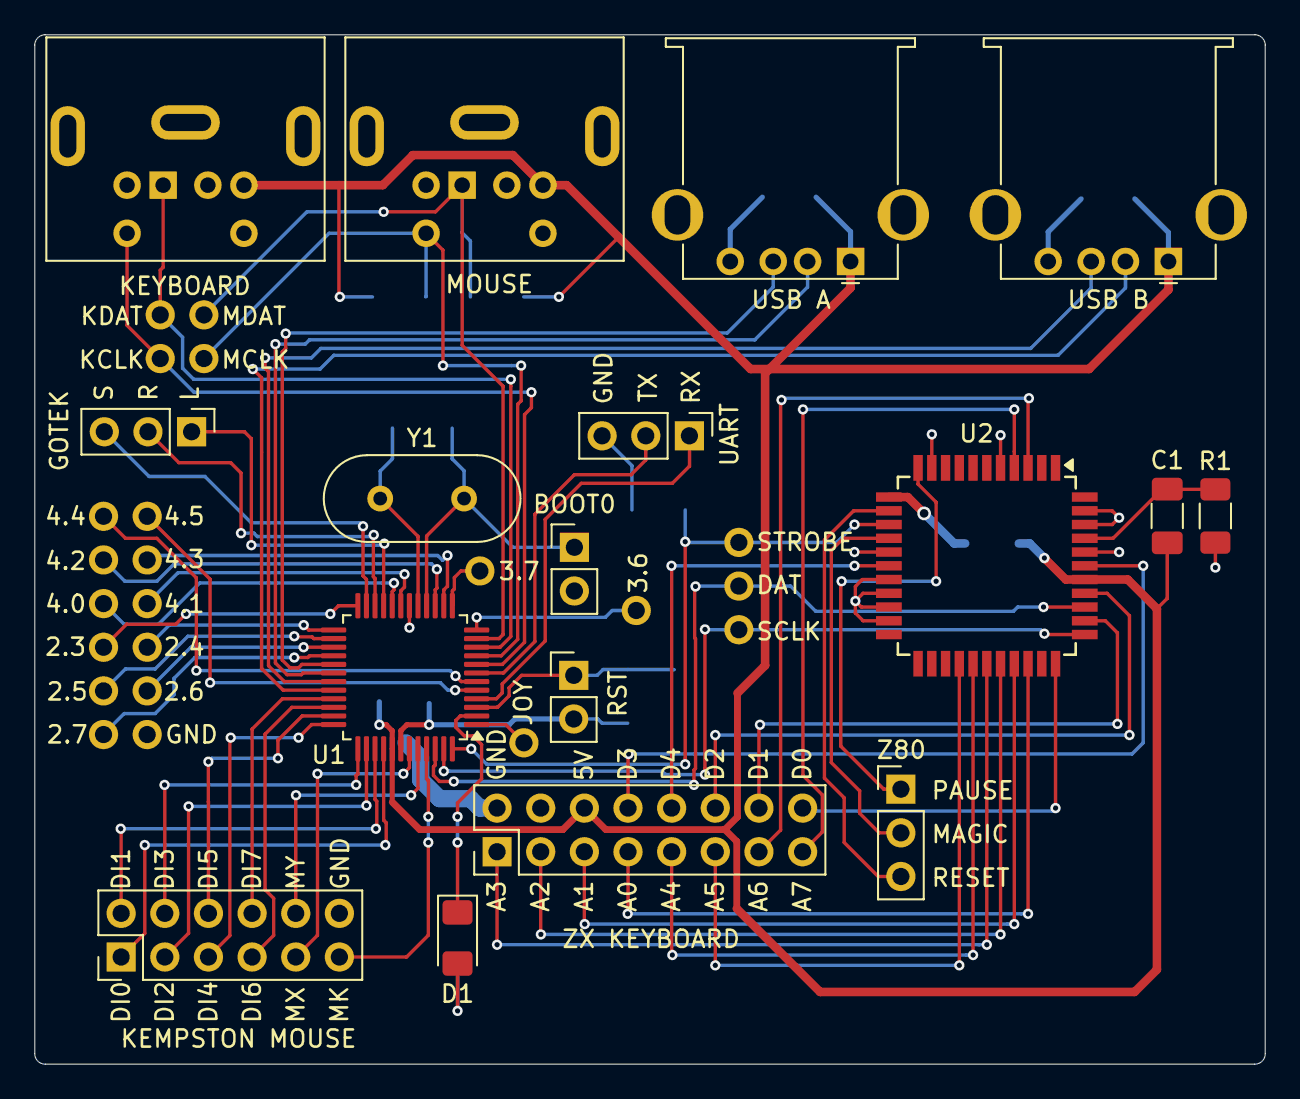
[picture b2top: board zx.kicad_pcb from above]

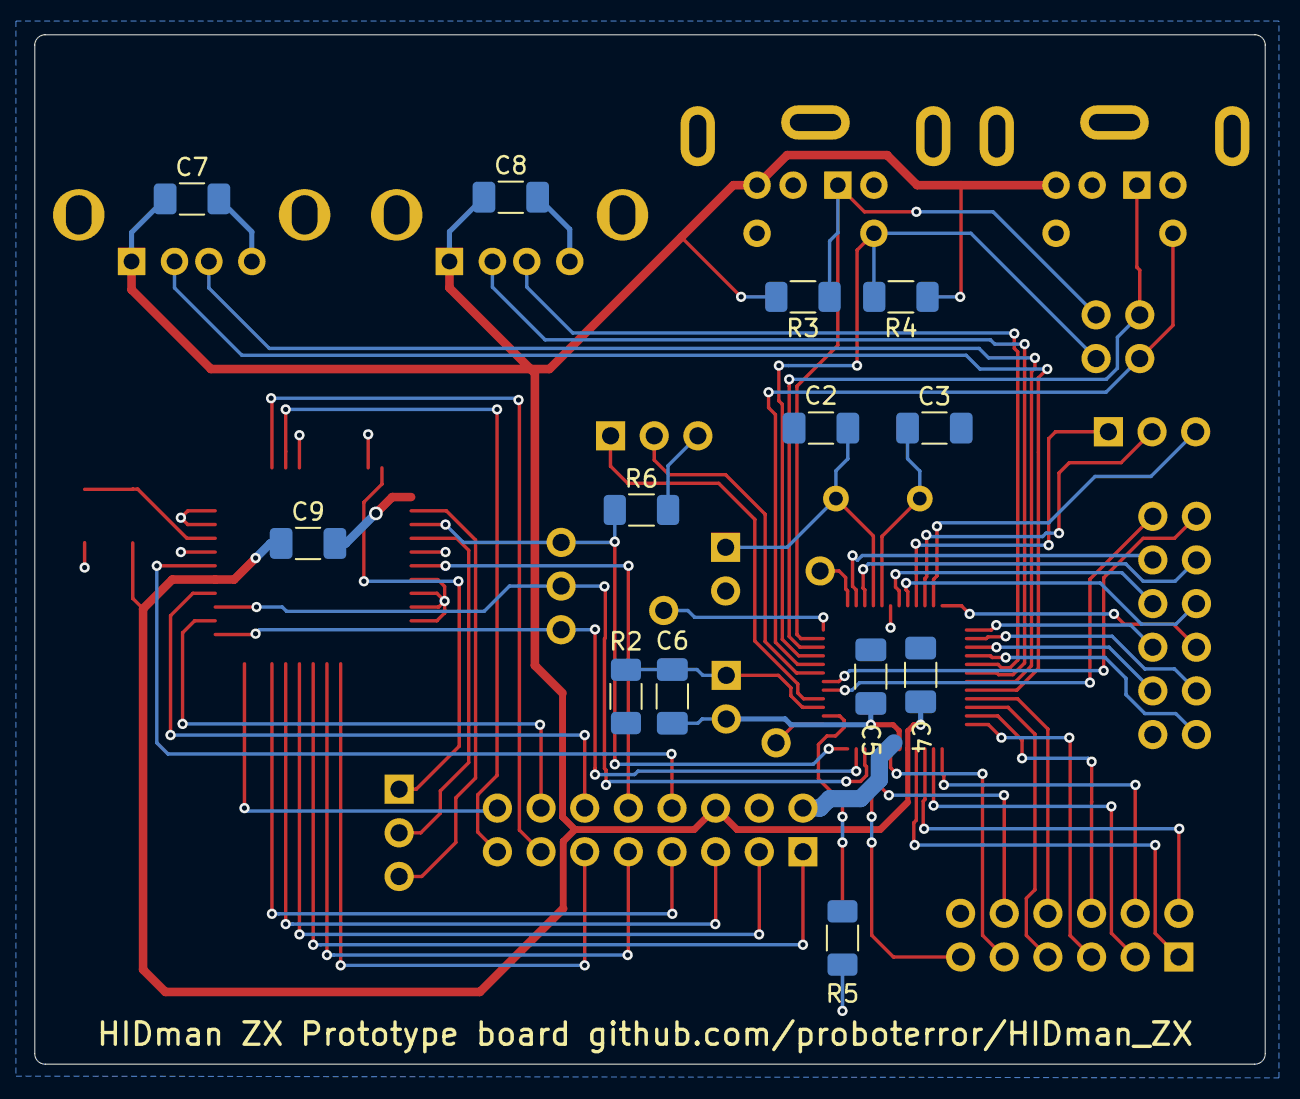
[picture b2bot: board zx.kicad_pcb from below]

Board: 2 copper layers, 71.6 x 59.9 mm, 52 parts (13 on the bottom side), 66 nets.
